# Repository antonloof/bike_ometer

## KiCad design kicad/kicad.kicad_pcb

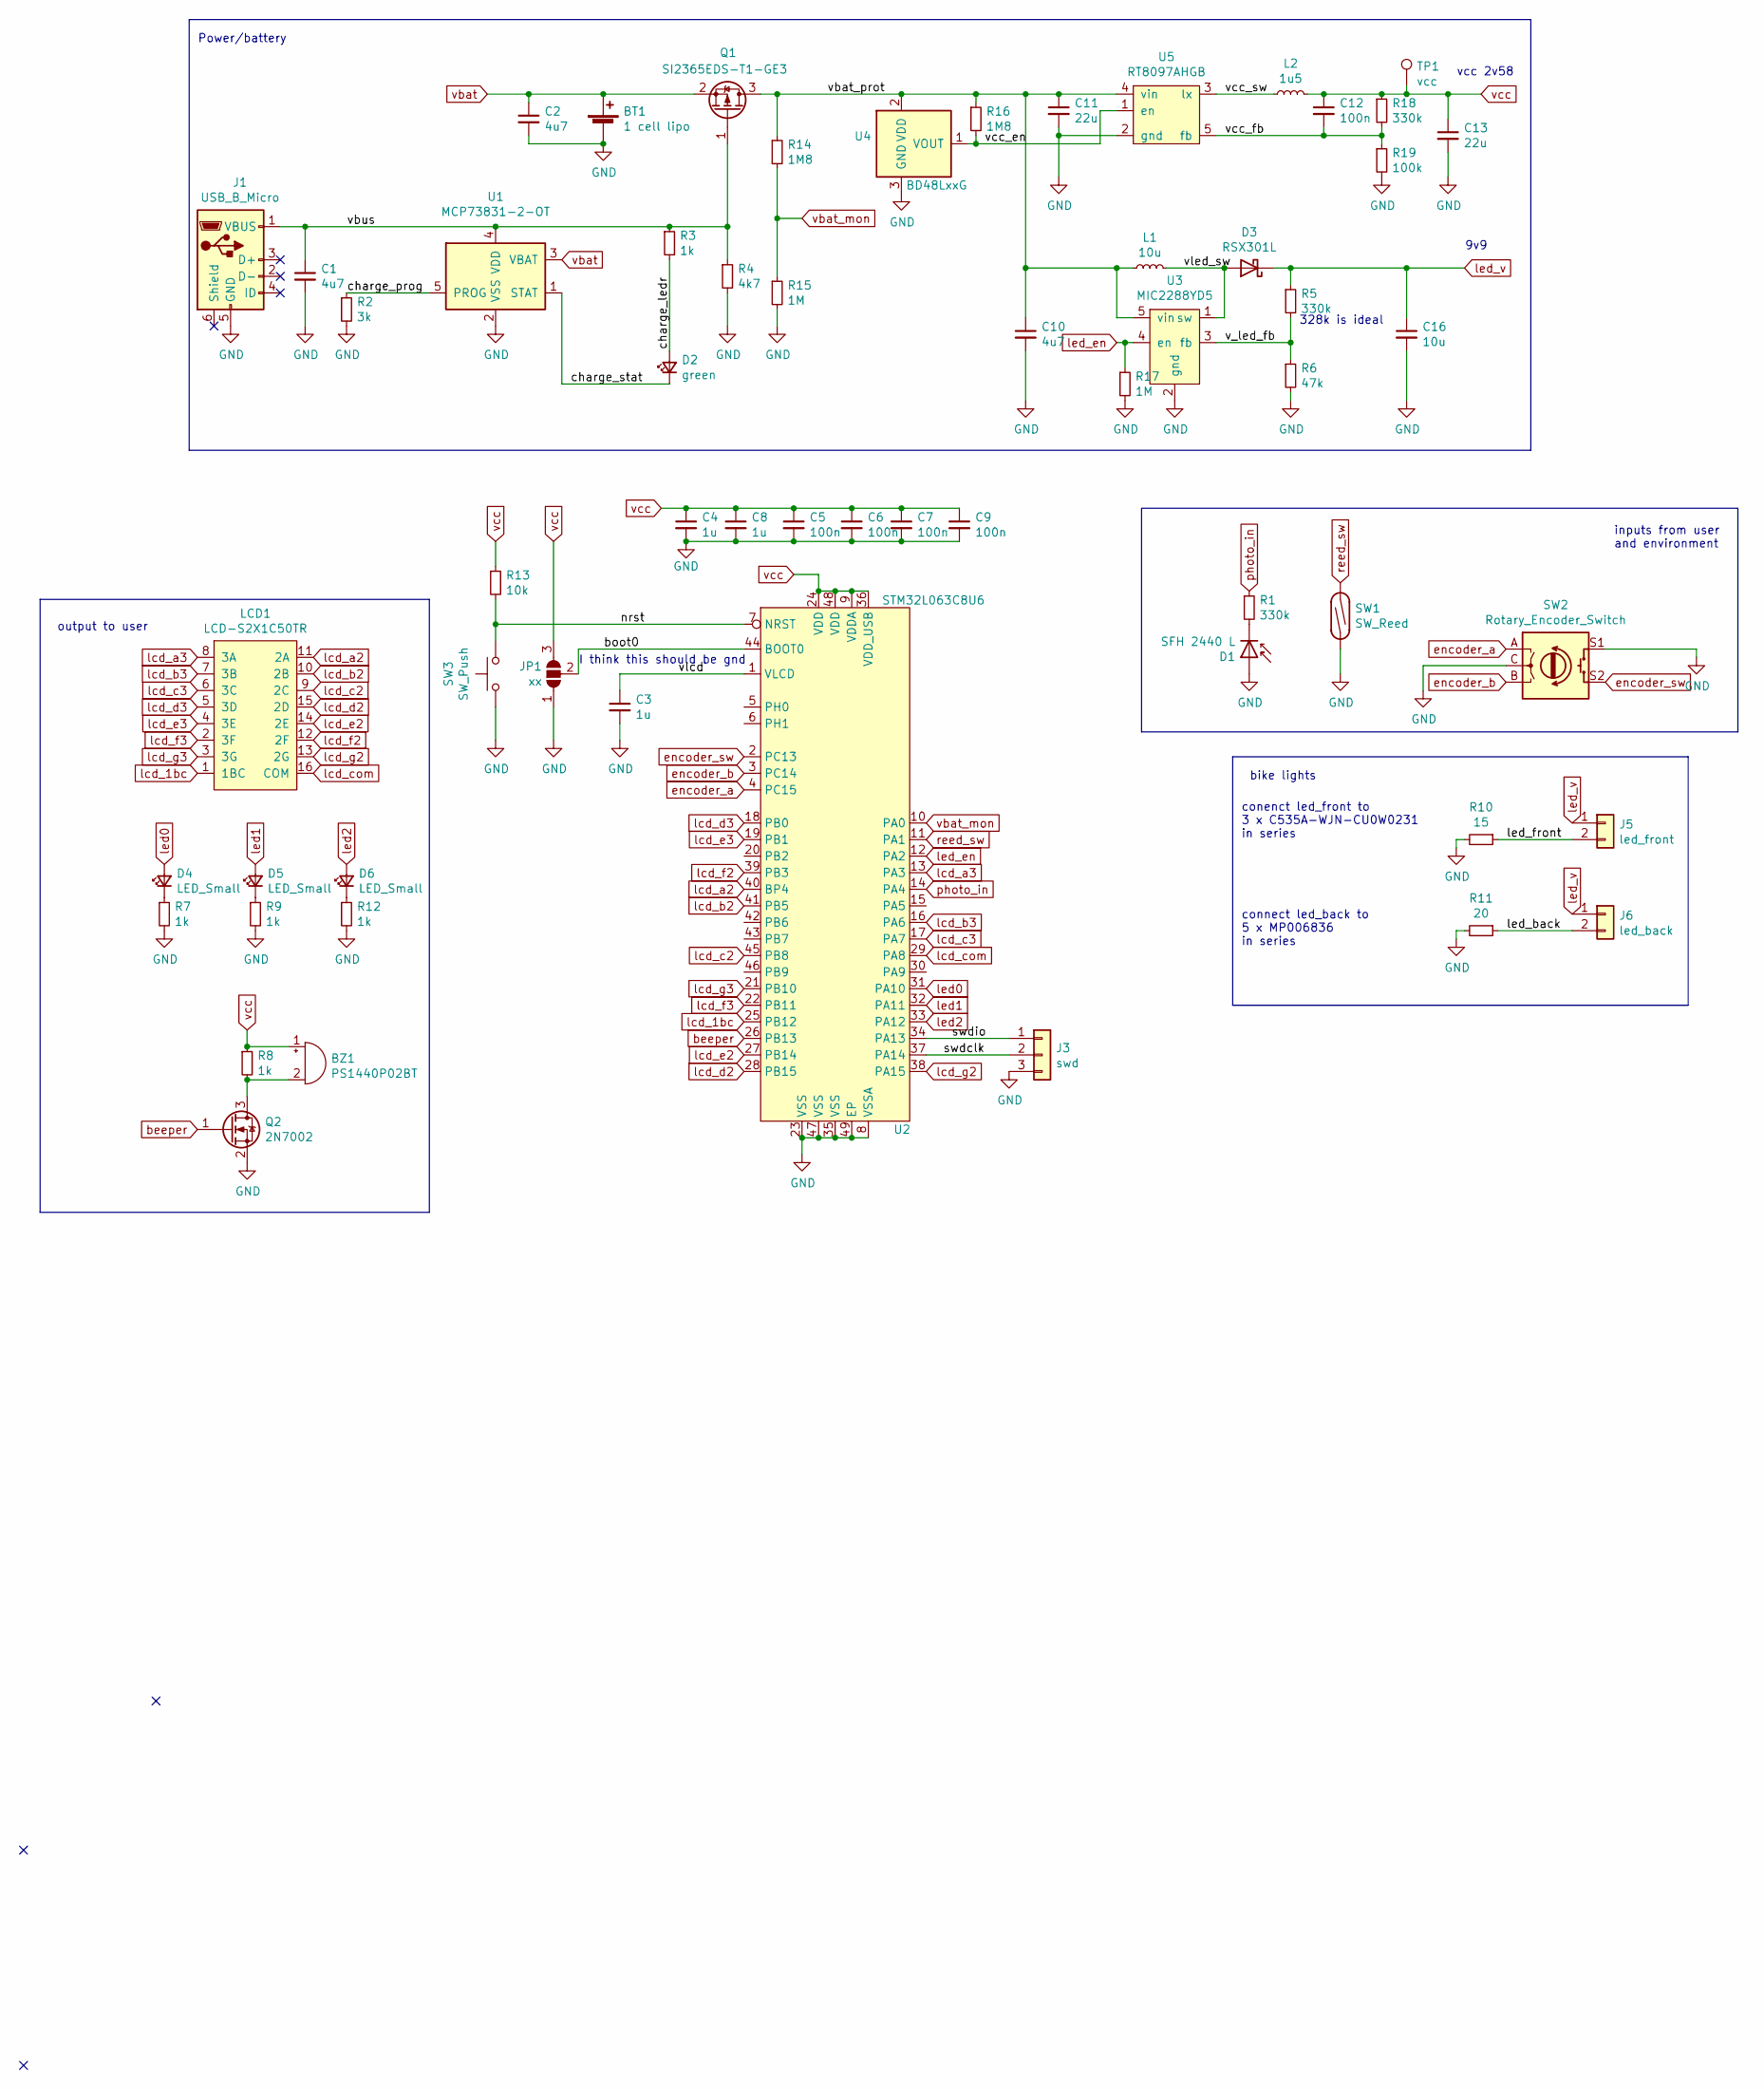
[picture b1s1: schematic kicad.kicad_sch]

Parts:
BT1: 1 cell lipo; PinHeader_1x02_P2.54mm_Vertical
BZ1: PS1440P02BT; buzzer_d14_p5
C1, C2, C10: 4u7; C_0603_1608Metric_Pad1.05x0.95mm_HandSolder
C3, C4, C8: 1u; C_0603_1608Metric_Pad1.05x0.95mm_HandSolder
C5, C6, C7, C9, C12: 100n; C_0603_1608Metric_Pad1.05x0.95mm_HandSolder
C11, C13: 22u; C_0603_1608Metric_Pad1.05x0.95mm_HandSolder
C16: 10u; C_0603_1608Metric_Pad1.05x0.95mm_HandSolder
D1: SFH 2440 L; sfh-2440-l
D2: green; LED_0603_1608Metric_Pad1.05x0.95mm_HandSolder
D3: RSX301L; SOD-106
D4, D5, D6: LED_Small; LED_0603_1608Metric_Pad1.05x0.95mm_HandSolder
J1: USB_B_Micro; USB_MICRO_10118193-0001LF
J3: swd; PinHeader_1x03_P2.54mm_Vertical
J5: led_front; PhoenixContact_MSTBVA_2,5_2-G_1x02_P5.00mm_Vertical
J6: led_back; PhoenixContact_MSTBVA_2,5_2-G_1x02_P5.00mm_Vertical
JP1: xx; SolderJumper-3_P1.3mm_Open_Pad1.0x1.5mm
L1: 10u; L_Wuerth_WE-PD-Typ-LS
L2: 1u5; L_Sunlord_MWSA0518_5.4x5.2mm
LCD1: LCD-S2X1C50TR
Q1: SI2365EDS-T1-GE3; SOT-23_Handsoldering
Q2: 2N7002; SOT-23
R1, R5, R18: 330k; R_0603_1608Metric_Pad1.05x0.95mm_HandSolder
R2: 3k; R_0603_1608Metric_Pad1.05x0.95mm_HandSolder
R3, R7, R8, R9, R12: 1k; R_0603_1608Metric_Pad1.05x0.95mm_HandSolder
R4: 4k7; R_0603_1608Metric_Pad1.05x0.95mm_HandSolder
R6: 47k; R_0603_1608Metric_Pad1.05x0.95mm_HandSolder
R10: 15; R_0603_1608Metric_Pad1.05x0.95mm_HandSolder
R11: 20; R_0603_1608Metric_Pad1.05x0.95mm_HandSolder
R13: 10k; R_0603_1608Metric_Pad1.05x0.95mm_HandSolder
R14, R16: 1M8; R_0603_1608Metric_Pad1.05x0.95mm_HandSolder
R15, R17: 1M; R_0603_1608Metric_Pad1.05x0.95mm_HandSolder
R19: 100k; R_0603_1608Metric_Pad1.05x0.95mm_HandSolder
SW1: SW_Reed; PhoenixContact_MSTBVA_2,5_2-G_1x02_P5.00mm_Vertical
SW2: Rotary_Encoder_Switch; RotaryEncoder_Alps_EC11E_Vertical_H20mm
SW3: SW_Push; push_sw_purple
TP1: vcc; TestPoint_Pad_1.5x1.5mm
U1: MCP73831-2-OT; SOT-23-5
U2: STM32L063C8U6; QFN-48-1EP_7x7mm_P0.5mm_EP5.6x5.6mm
U3: MIC2288YD5; SOT-23-5_HandSoldering
U4: BD48LxxG; SOT-23
U5: RT8097AHGB; SOT-23-5_HandSoldering

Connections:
/boot0: JP1.2 (C), U2.44 (BOOT0)
/charge_ledr: D2.2 (A), R3.2
/charge_prog: R2.1, U1.5 (PROG)
/charge_stat: D2.1 (K), U1.1 (STAT)
/led_back: J6.2, R11.1
/led_front: J5.2, R10.1
/nrst: R13.2, SW3.2, U2.7 (NRST)
/swdclk: J3.2, U2.37 (PA14)
/swdio: J3.1, U2.34 (PA13)
/v_led_fb: R5.2, R6.1, U3.3 (fb)
/vbat_prot: C10.1, C11.1, L1.1, Q1.3 (D), R14.1, R16.1, U3.5 (vin), U4.2 (VDD), U5.4 (vin)
/vbus: C1.1, J1.1 (VBUS), Q1.1 (G), R3.1, R4.1, U1.4 (VDD)
/vcc_en: R16.2, U4.1 (VOUT), U5.1 (en)
/vcc_fb: C12.2, R18.2, R19.1, U5.5 (fb)
/vcc_sw: L2.1, U5.3 (lx)
/vlcd: C3.1, U2.1 (VLCD)
/vled_sw: D3.2 (A), L1.2, U3.1 (sw)
GND: BT1.2 (-), C1.2, C2.2, C3.2, C4.2, C5.2, C6.2, C7.2, C8.2, C9.2, C10.2, C11.2, C13.2, C16.2, D1.2 (A), J1.5 (GND), J3.3, JP1.1 (A), Q2.2 (S), R2.2, R4.2, R6.2, R7.2, R9.2, R10.2, R11.2, R12.2, R15.2, R17.2, R19.2, SW1.2, SW2.C, SW2.S1, SW3.1, U1.2 (VSS), U2.8 (VSSA), U2.23 (VSS), U2.35 (VSS), U2.47 (VSS), U2.49 (EP), U3.2 (gnd), U4.3 (GND), U5.2 (gnd)
unnamed: BZ1.2 (+), Q2.3 (D), R8.2
unnamed: D1.1 (K), R1.2
unnamed: D4.1 (K), R7.1
unnamed: D5.1 (K), R9.1
unnamed: D6.1 (K), R12.1
beeper: Q2.1 (G), U2.26 (PB13)
encoder_a: SW2.A, U2.4 (PC15)
encoder_b: SW2.B, U2.3 (PC14)
encoder_sw: SW2.S2, U2.2 (PC13)
lcd_1bc: LCD1.1 (1BC), U2.25 (PB12)
lcd_a2: LCD1.11 (2A), U2.40 (BP4)
lcd_a3: LCD1.8 (3A), U2.13 (PA3)
lcd_b2: LCD1.10 (2B), U2.41 (PB5)
lcd_b3: LCD1.7 (3B), U2.16 (PA6)
lcd_c2: LCD1.9 (2C), U2.45 (PB8)
lcd_c3: LCD1.6 (3C), U2.17 (PA7)
lcd_com: LCD1.16 (COM), U2.29 (PA8)
lcd_d2: LCD1.15 (2D), U2.28 (PB15)
lcd_d3: LCD1.5 (3D), U2.18 (PB0)
lcd_e2: LCD1.14 (2E), U2.27 (PB14)
lcd_e3: LCD1.4 (3E), U2.19 (PB1)
lcd_f2: LCD1.12 (2F), U2.39 (PB3)
lcd_f3: LCD1.2 (3F), U2.22 (PB11)
lcd_g2: LCD1.13 (2G), U2.38 (PA15)
lcd_g3: LCD1.3 (3G), U2.21 (PB10)
led0: D4.2 (A), U2.31 (PA10)
led1: D5.2 (A), U2.32 (PA11)
led2: D6.2 (A), U2.33 (PA12)
led_en: R17.1, U2.12 (PA2), U3.4 (en)
led_v: C16.1, D3.1 (K), J5.1, J6.1, R5.1
photo_in: R1.1, U2.14 (PA4)
reed_sw: SW1.1, U2.11 (PA1)
vbat: BT1.1 (+), C2.1, Q1.2 (S), U1.3 (VBAT)
vbat_mon: R14.2, R15.1, U2.10 (PA0)
vcc: BZ1.1 (-), C4.1, C5.1, C6.1, C7.1, C8.1, C9.1, C12.1, C13.1, JP1.3 (B), L2.2, R8.1, R13.1, R18.1, TP1.1, U2.9 (VDDA), U2.24 (VDD), U2.36 (VDD_USB), U2.48 (VDD)

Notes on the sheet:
328k is ideal
I think this should be gnd
connect led_back to 5 x MP006836 in series
bike lights
9v9
vcc 2v58
Power/battery
output to user
inputs from user and environment
conenct led_front to 3 x C535A-WJN-CU0W0231 in series

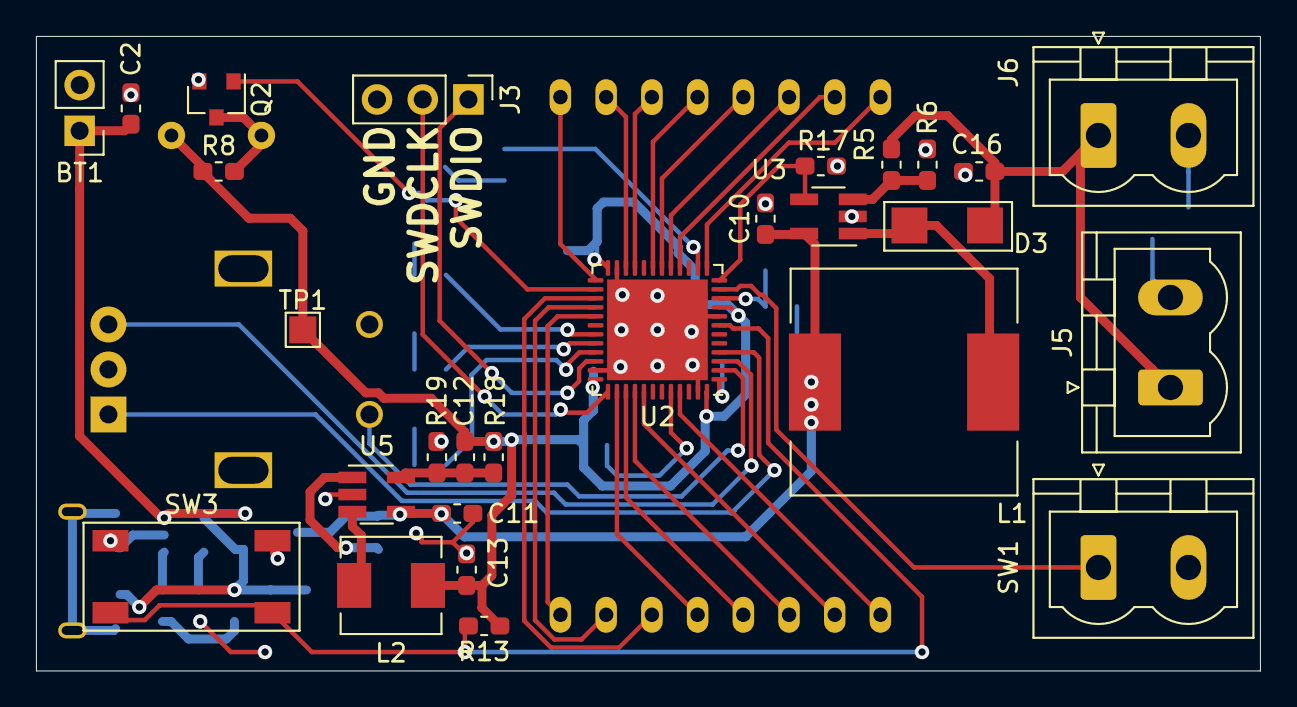
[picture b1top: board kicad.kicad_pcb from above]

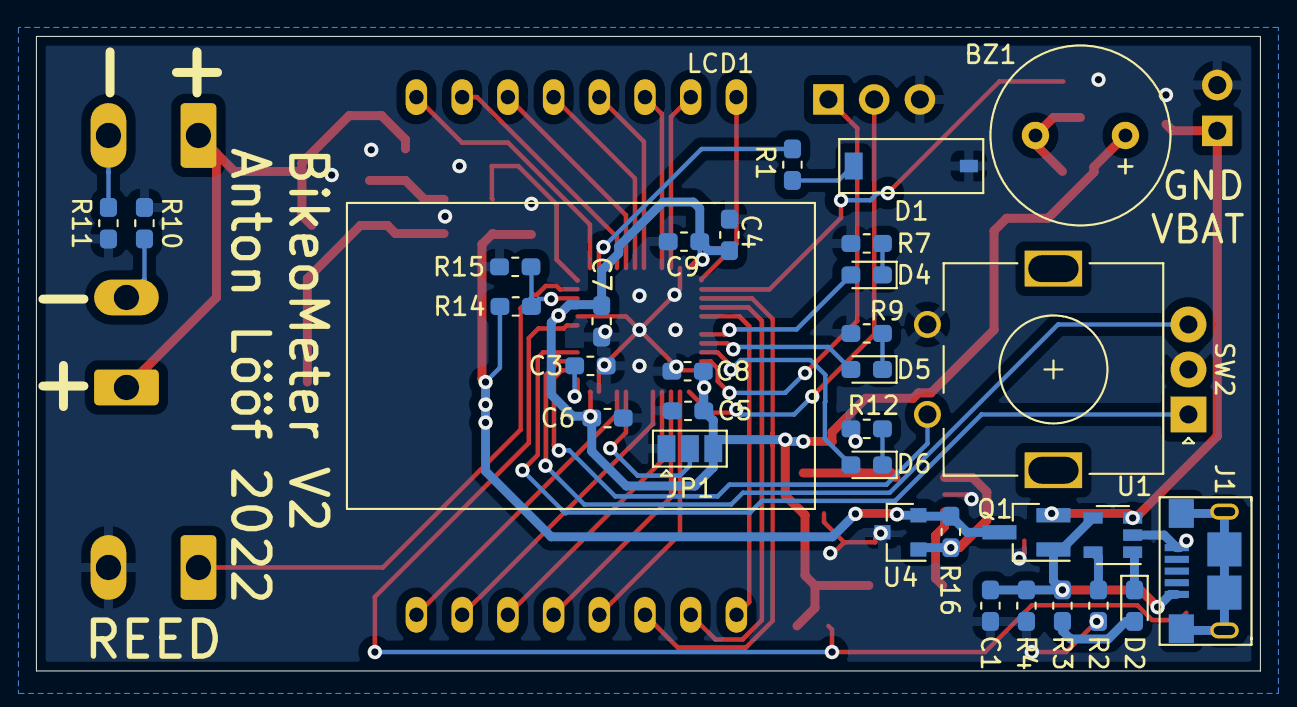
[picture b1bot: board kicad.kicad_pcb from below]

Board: 2 copper layers, 68.0 x 35.2 mm, 60 parts (33 on the bottom side), 53 nets.

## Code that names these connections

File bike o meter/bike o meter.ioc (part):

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Mcu.Name=STM32L063C8Tx
Mcu.Package=LQFP48
Mcu.UserName=STM32L063C8Tx
PA0.GPIOParameters=GPIO_Label
PA0.GPIO_Label=encoder_sw
PA0.Signal=GPIO_Input
PA1.Mode=SEG0
PA1.Signal=LCD_SEG0
PA10.GPIOParameters=GPIO_Label
PA10.GPIO_Label=spi_cs_0
PA10.Signal=GPIO_Input
PA11.Mode=Full_Duplex_Master
PA11.Signal=SPI1_MISO
PA12.Mode=Full_Duplex_Master
PA12.Signal=SPI1_MOSI
PA13.Mode=Serial_Wire
PA13.Signal=SYS_SWDIO
PA14.Mode=Serial_Wire
PA14.Signal=SYS_SWCLK
PA2.Mode=SEG1
PA2.Signal=LCD_SEG1
PA3.Mode=SEG2
PA3.Signal=LCD_SEG2
PA4.GPIOParameters=GPIO_Label
PA4.GPIO_Label=photo_in
PA4.Mode=IN4
PA4.Signal=ADC_IN4
PA5.Mode=Full_Duplex_Master
PA5.Signal=SPI1_SCK
PA6.Mode=SEG3
PA6.Signal=LCD_SEG3
PA7.Mode=SEG4
PA7.Signal=LCD_SEG4
PA8.Mode=Static
PA8.Signal=LCD_COM0
PA9.GPIOParameters=GPIO_Label
PA9.GPIO_Label=spi_cs_1
PA9.Signal=GPIO_Input
PB0.Mode=SEG5
PB0.Signal=LCD_SEG5
PB1.Mode=SEG6
PB1.Signal=LCD_SEG6
PB10.Mode=SEG10
PB10.Signal=LCD_SEG10
PB11.Mode=SEG11
PB11.Signal=LCD_SEG11
PB12.Mode=SEG12
PB12.Signal=LCD_SEG12
PB13.Mode=SEG13
PB13.Signal=LCD_SEG13
PB14.Mode=SEG14
PB14.Signal=LCD_SEG14
PB3.Mode=SEG7
PB3.Signal=LCD_SEG7
PB4.Mode=SEG8
PB4.Signal=LCD_SEG8
PB5.Mode=SEG9
PB5.Signal=LCD_SEG9
PB6.GPIOParameters=GPIO_Pu
PB6.GPIO_Pu=GPIO_PULLUP
PB6.Mode=I2C
PB6.Signal=I2C1_SCL
PB7.GPIOParameters=GPIO_Pu
PB7.GPIO_Pu=GPIO_PULLUP
PB7.Mode=I2C
PB7.Signal=I2C1_SDA
PB8.GPIOParameters=GPIO_Label
PB8.GPIO_Label=reed_sw
PB8.Signal=GPIO_Input
PB9.GPIOParameters=GPIO_Label
PB9.GPIO_Label=led_en
PB9.Signal=GPIO_Output
PC13.GPIOParameters=GPIO_Label
PC13.GPIO_Label=led0
PC13.Signal=GPIO_Output
PC14-OSC32_IN.GPIOParameters=GPIO_Label
PC14-OSC32_IN.GPIO_Label=led1
PC14-OSC32_IN.Signal=GPIO_Output
PC15-OSC32_OUT.GPIOParameters=GPIO_Label
PC15-OSC32_OUT.GPIO_Label=led2
PC15-OSC32_OUT.Signal=GPIO_Output
PH0-OSC_IN.GPIOParameters=GPIO_Label
PH0-OSC_IN.GPIO_Label=encoder_a
PH0-OSC_IN.Signal=GPIO_Input
PH1-OSC_OUT.GPIOParameters=GPIO_Label
PH1-OSC_OUT.GPIO_Label=encoder_b
PH1-OSC_OUT.Signal=GPIO_Input
RCC.HSE_VALUE=8000000
RCC.SYSCLKFreq_VALUE=2097000
board=custom

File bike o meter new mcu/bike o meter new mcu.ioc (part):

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Mcu.Name=STM32L152R(6-8-B)HxA
Mcu.Package=TFBGA64
Mcu.UserName=STM32L152R6HxA
PA0-WKUP1.GPIOParameters=GPIO_Label
PA0-WKUP1.GPIO_Label=photo_in
PA0-WKUP1.Mode=IN0
PA0-WKUP1.Signal=ADC_IN0
PA1.Mode=SEG0
PA1.Signal=LCD_SEG0
PA11.Mode=Full_Duplex_Master
PA11.Signal=SPI1_MISO
PA12.Mode=Full_Duplex_Master
PA12.Signal=SPI1_MOSI
PA13.Mode=Serial_Wire
PA13.Signal=SYS_JTMS-SWDIO
PA14.Mode=Serial_Wire
PA14.Signal=SYS_JTCK-SWCLK
PA15.GPIOParameters=GPIO_Label
PA15.GPIO_Label=reed_sw
PA15.Signal=S_TIM2_CH1_ETR
PA2.Mode=SEG1
PA2.Signal=LCD_SEG1
PA3.Mode=SEG2
PA3.Signal=LCD_SEG2
PA5.Mode=Full_Duplex_Master
PA5.Signal=SPI1_SCK
PA6.Mode=SEG3
PA6.Signal=LCD_SEG3
PA7.Mode=SEG4
PA7.Signal=LCD_SEG4
PA8.Mode=Static
PA8.Signal=LCD_COM0
PA9.GPIOParameters=GPIO_Label
PA9.GPIO_Label=spi_cs_0
PA9.Signal=GPIO_Output
PB0.Mode=SEG5
PB0.Signal=LCD_SEG5
PB1.Mode=SEG6
PB1.Signal=LCD_SEG6
PB10.Mode=SEG10
PB10.Signal=LCD_SEG10
PB11.Mode=SEG11
PB11.Signal=LCD_SEG11
PB12.Mode=SEG12
PB12.Signal=LCD_SEG12
PB13.Mode=SEG13
PB13.Signal=LCD_SEG13
PB14.Mode=SEG14
PB14.Signal=LCD_SEG14
PB3.Mode=SEG7
PB3.Signal=LCD_SEG7
PB4.Mode=SEG8
PB4.Signal=LCD_SEG8
PB5.Mode=SEG9
PB5.Signal=LCD_SEG9
PB8.Mode=I2C
PB8.Signal=I2C1_SCL
PB9.Mode=I2C
PB9.Signal=I2C1_SDA
PC0.GPIOParameters=GPIO_Label
PC0.GPIO_Label=led2
PC0.Signal=GPIO_Output
PC1.GPIOParameters=GPIO_Label
PC1.GPIO_Label=led1
PC1.Signal=GPIO_Output
PC10.GPIOParameters=GPIO_Label
PC10.GPIO_Label=spi_cs_1
PC10.Signal=GPIO_Output
PC11.GPIOParameters=GPIO_Label
PC11.GPIO_Label=led_en
PC11.Signal=GPIO_Output
PC13-WKUP2.GPIOParameters=GPIO_Label
PC13-WKUP2.GPIO_Label=encoder_sw
PC13-WKUP2.Mode=SYS_WakeUp1
PC13-WKUP2.Signal=SYS_WKUP2
PC14-OSC32_IN.GPIOParameters=GPIO_Label
PC14-OSC32_IN.GPIO_Label=encoder_a
PC14-OSC32_IN.Signal=GPXTI14
PC15-OSC32_OUT.GPIOParameters=GPIO_Label
PC15-OSC32_OUT.GPIO_Label=encoder_b
PC15-OSC32_OUT.Signal=GPIO_Input
PC2.GPIOParameters=GPIO_Label
PC2.GPIO_Label=led0
PC2.Signal=GPIO_Output
PD2.GPIOParameters=GPIO_Label
PD2.GPIO_Label=beeper
PD2.Signal=GPIO_Output
RCC.HSE_VALUE=24000000
RCC.SYSCLKFreq_VALUE=2097000
board=custom

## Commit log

2021-06-16 Add schema and basic SW tests
2021-07-03 Use a mcu in stock ...
2021-10-19 version updates
2021-10-19 Some schema work with correct mcu
    also rm some shit
2021-10-21 Place n route
2021-10-24 rev1 pcb done
2022-01-11 Rev2 psb with correct mcu size...
